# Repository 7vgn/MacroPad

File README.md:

# MacroPad

> [!NOTE]
> This project is still under development. While almost everything works on Linux, Windows is a mess.

## What is This?
MacroPad is a USB input device with six keys, three rotary encoders, a slider,
and three OLED displays. All controls can be configured to send user-defined
mouse or keyboard input to the computer. Multiple profiles are supported,
allowing you to change between different key-assignments with the press of a
button. Typical applications include audio and video editing, computer graphics,
and presentations.

MacroPad implements standard USB HID (human interface) device classes and thus
requires no driver. The only is software that is needed is a [Program for
Configuring](Software/) it and potentially some [software for the slider](SliderApps/).

MacroPad is powered by a
[Raspberry Pi Pico](https://www.raspberrypi.com/documentation/microcontrollers/raspberry-pi-pico.html)
using the RP2040 microcontroller.

## How Does It Work?
When plugged into a computer, MacroPad presents itself as a three-in-one
input device composed of a keyboard, a mouse, and a miscellaneous input device.
All keys and rotary encoders can be configured to send keyboard or mouse input
to the computer.

The slider is also an HID-class device that needs no driver. However, most
operating systems don't know what to do with slider input and so they just
ignore it. For that reason, you will most likely want to have a piece of
software running that consumes these inputs and performs certain actions,
like adjusting volume or changing the brush size in a drawing application. 
You can find several examples in the [SliderApps](SliderApps/) folder.

## Can I Have One?
MacroPad is not sold anywhere. In this repository, you can find all the
necessary information and code to build a MacroPad yourself. Please have a look
at the [Building Instructions](Documentation/BuildingInstructions.pdf) and
the [User's Guide](Documentation/UsersGuide.pdf).
Building a MacroPad is not particularly difficult. As long as you can hold a
soldering iron without touching the wrong end, you should be fine.

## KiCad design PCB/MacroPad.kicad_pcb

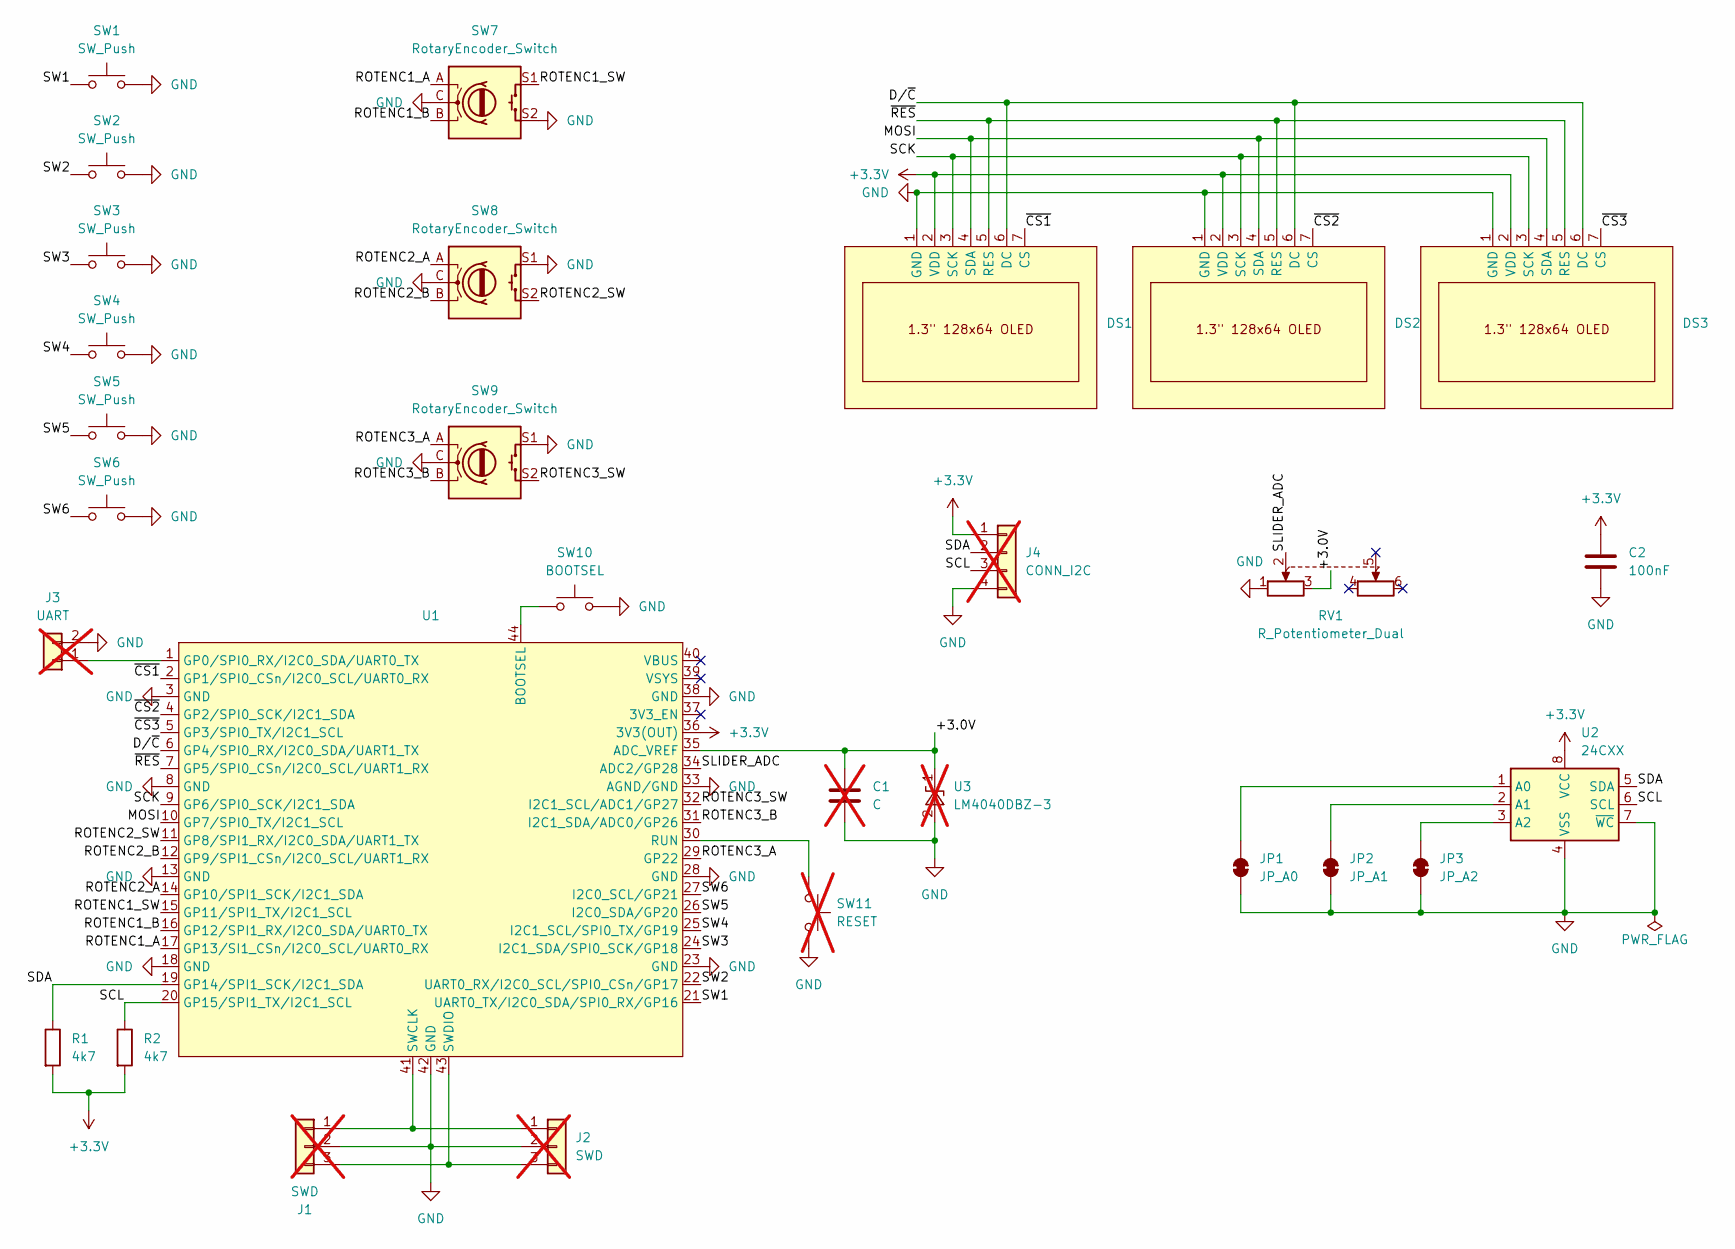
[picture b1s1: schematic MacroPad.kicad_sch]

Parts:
C1: C; C_1206_3216Metric_Pad1.33x1.80mm_HandSolder; not fitted
C2: 100nF; C_1206_3216Metric_Pad1.33x1.80mm_HandSolder
DS1, DS2, DS3: OLED 1.3in
J1: SWD; PinHeader_1x03_P2.54mm_Horizontal; not fitted
J2: SWD; JST_SH_SM03B-SRSS-TB_1x03-1MP_P1.00mm_Horizontal; not fitted
J3: UART; PinHeader_1x02_P2.54mm_Horizontal; not fitted
J4: CONN_I2C; PinHeader_1x04_P2.54mm_Horizontal; not fitted
JP1: JP_A0; SolderJumper-2_P1.3mm_Bridged_RoundedPad1.0x1.5mm
JP2: JP_A1; SolderJumper-2_P1.3mm_Bridged_RoundedPad1.0x1.5mm
JP3: JP_A2; SolderJumper-2_P1.3mm_Bridged_RoundedPad1.0x1.5mm
R1, R2: 4k7; R_1206_3216Metric_Pad1.30x1.75mm_HandSolder
RV1: R_Potentiometer_Dual; ALPS_RS60112
SW1, SW2, SW3, SW4, SW5, SW6: SW_Push; SW_Cherry_MX_1.00u_PCB
SW7, SW8, SW9: RotaryEncoder_Switch; RotaryEncoder_Alps_EC11E-Switch_Vertical_H20mm
SW10: BOOTSEL; MicroSwitch
SW11: RESET; MicroSwitch; not fitted
U1: RPi_Pico_SMD_TH
U2: 24CXX; SOIC-8_3.9x4.9mm_P1.27mm
U3: LM4040DBZ-3; SOT-23; not fitted

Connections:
+3.3V: C2.1, DS1.2 (VDD), DS2.2 (VDD), DS3.2 (VDD), J4.1, R1.2, R2.2, U1.36 (3V3(OUT)), U2.8 (VCC)
/+3.0V: C1.1, RV1.3, U1.35 (ADC_VREF), U3.1 (K)
/D/~C: DS1.6 (DC), DS2.6 (DC), DS3.6 (DC), U1.6 (GP4/SPI0_RX/I2C0_SDA/UART1_TX)
/MOSI: DS1.4 (SDA), DS2.4 (SDA), DS3.4 (SDA), U1.10 (GP7/SPI0_TX/I2C1_SCL)
/ROTENC1_A: SW7.A, U1.17 (GP13/SI1_CSn/I2C0_SCL/UART0_RX)
/ROTENC1_B: SW7.B, U1.16 (GP12/SPI1_RX/I2C0_SDA/UART0_TX)
/ROTENC1_SW: SW7.S1, U1.15 (GP11/SPI1_TX/I2C1_SCL)
/ROTENC2_A: SW8.A, U1.14 (GP10/SPI1_SCK/I2C1_SDA)
/ROTENC2_B: SW8.B, U1.12 (GP9/SPI1_CSn/I2C0_SCL/UART1_RX)
/ROTENC2_SW: SW8.S2, U1.11 (GP8/SPI1_RX/I2C0_SDA/UART1_TX)
/ROTENC3_A: SW9.A, U1.29 (GP22)
/ROTENC3_B: SW9.B, U1.31 (I2C1_SDA/ADC0/GP26)
/ROTENC3_SW: SW9.S2, U1.32 (I2C1_SCL/ADC1/GP27)
/SCK: DS1.3 (SCK), DS2.3 (SCK), DS3.3 (SCK), U1.9 (GP6/SPI0_SCK/I2C1_SDA)
/SCL: J4.3, R2.1, U1.20 (GP15/SPI1_TX/I2C1_SCL), U2.6 (SCL)
/SDA: J4.2, R1.1, U1.19 (GP14/SPI1_SCK/I2C1_SDA), U2.5 (SDA)
/SLIDER_ADC: RV1.2, U1.34 (ADC2/GP28)
/SW1: SW1.1, U1.21 (UART0_TX/I2C0_SDA/SPI0_RX/GP16)
/SW2: SW2.1, U1.22 (UART0_RX/I2C0_SCL/SPI0_CSn/GP17)
/SW3: SW3.1, U1.24 (I2C1_SDA/SPI0_SCK/GP18)
/SW4: SW4.1, U1.25 (I2C1_SCL/SPI0_TX/GP19)
/SW5: SW5.1, U1.26 (I2C0_SDA/GP20)
/SW6: SW6.1, U1.27 (I2C0_SCL/GP21)
/~CS1: DS1.7 (CS), U1.2 (GP1/SPI0_CSn/I2C0_SCL/UART0_RX)
/~CS2: DS2.7 (CS), U1.4 (GP2/SPI0_SCK/I2C1_SDA)
/~CS3: DS3.7 (CS), U1.5 (GP3/SPI0_TX/I2C1_SCL)
/~RES: DS1.5 (RES), DS2.5 (RES), DS3.5 (RES), U1.7 (GP5/SPI0_CSn/I2C0_SCL/UART1_RX)
GND: C1.2, C2.2, DS1.1 (GND), DS2.1 (GND), DS3.1 (GND), J1.2, J2.2, J3.2, J4.4, JP1.1 (A), JP2.1 (A), JP3.1 (A), RV1.1, SW1.2, SW2.2, SW3.2, SW4.2, SW5.2, SW6.2, SW7.C, SW7.S2, SW8.C, SW8.S1, SW9.C, SW9.S1, SW10.2, SW11.2, U1.3 (GND), U1.8 (GND), U1.13 (GND), U1.18 (GND), U1.23 (GND), U1.28 (GND), U1.33 (AGND/GND), U1.38 (GND), U1.42 (GND), U2.4 (VSS), U2.7 (~WC), U3.2 (A)
unnamed: J1.1, J2.1, U1.41 (SWCLK)
unnamed: J1.3, J2.3, U1.43 (SWDIO)
unnamed: J3.1, U1.1 (GP0/SPI0_RX/I2C0_SDA/UART0_TX)
unnamed: JP1.2 (B), U2.1 (A0)
unnamed: JP2.2 (B), U2.2 (A1)
unnamed: JP3.2 (B), U2.3 (A2)
unnamed: SW10.1, U1.44 (BOOTSEL)
unnamed: SW11.1, U1.30 (RUN)

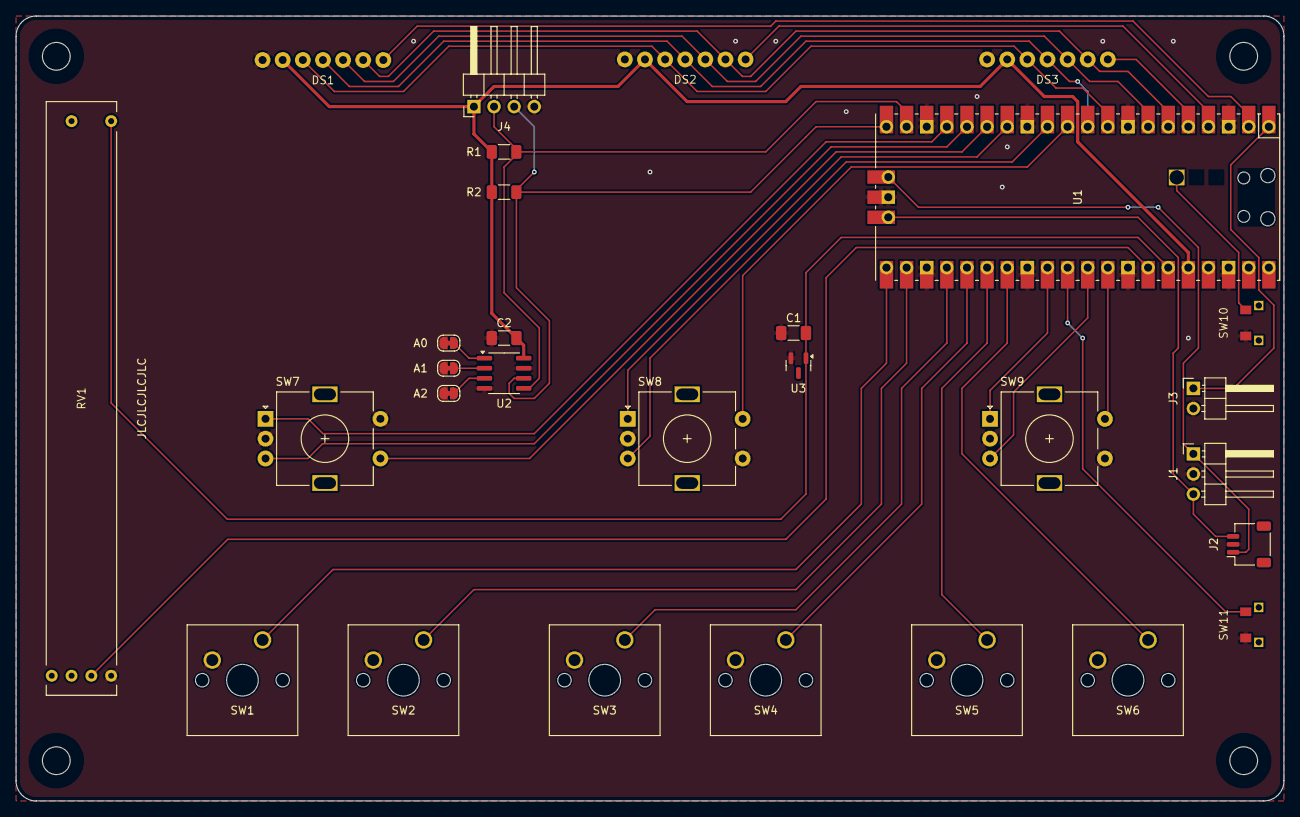
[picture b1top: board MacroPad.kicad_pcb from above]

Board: 2 copper layers, 160.0 x 99.1 mm, 29 parts (0 on the bottom side), 36 nets.

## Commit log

2024-10-13 Fixed broken link to title image
